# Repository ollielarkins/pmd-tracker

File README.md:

# PMD Tracker

A wearable performance tracker for rugby. It sits in a jersey pouch between the shoulder blades, records a player's match, and syncs the results to a companion app for review after the game.

*KiCad 3D render of the 45 x 30 mm 4-layer board (not yet fabricated).*

## What it measures

| Area | Metrics |
|---|---|
| Locomotion | distance, max speed, sprint count and sprint distance |
| Contact load | impact count, peak g, total load, impacts by intensity band |
| Position | time-on-pitch heatmap (10 m cells), work rate in m/min |

## How it works

1. **Sensing.** A u-blox MAX-M10S GNSS module gives position at 10 Hz. An ADXL372 high-g accelerometer (±200 g) catches impacts that a normal IMU would clip. An LSM6DSO 6-axis IMU is part of the design but is not used by the metrics yet.
2. **On-device metrics.** The nRF52840 runs Zephyr RTOS. Every fix and accel sample goes through [`firmware/lib/metrics`](firmware/lib/metrics), which is portable C:
   - **Position.** Each fix is projected to metres from a pitch origin.
   - **Distance.** Fixes that imply more than 12 m/s are rejected as GNSS glitches. Steps under 0.3 m/s count as standing jitter and add no distance.
   - **Speed and sprints.** Speed is an exponential moving average. A sprint starts above 7 m/s and ends below 6 m/s. It only counts if it lasts at least 1 s.
   - **Impacts.** An impact starts when |a| ≥ 8 g. Samples in the next 250 ms count as the same hit, and its peak is the hit's intensity.
   - **Heatmap.** The time spent at each position is binned into a grid in the pitch frame.
3. **Storage.** A summary checkpoint is written to flash (NVS) every 10 s, so a battery pull mid-match keeps the totals.
4. **Sync.** The device advertises over Bluetooth LE as `PMD`. The app reads one 228-byte summary characteristic (layout in [`metrics.h`](firmware/lib/metrics/metrics.h)). It writes the reset characteristic to start a new session.

Every threshold above sits in one `pmd_config` struct. They are starting values and still need calibrating against real sessions.

## Design targets

The device is designed against World Rugby Law 4.3(m), Regulation 12 and the Player Monitoring Device Performance Specification:

- total mass under 90 g
- no surface radius below 12 mm
- enclosure survives the specification's impact test and 2.5 kN compression test without rupture

| Part | Component |
|---|---|
| MCU | nRF52840 (BLE 5) in a Raytac MDBT50Q-1MV2 module, on a custom 4-layer PCB |
| GNSS | u-blox MAX-M10S, 10 Hz |
| High-g accel | ADXL372 |
| IMU | LSM6DSO |
| Battery | 500 mAh LiPo |

The BOM is in [`hardware/bom.csv`](hardware/bom.csv).

## Hardware

The board is a 45 x 30 mm, 4-layer PCB designed in KiCad 10: [`hardware/kicad`](hardware/kicad).

| Layer | Use |
|---|---|
| F.Cu | parts, signals, GND pour |
| In1.Cu | solid GND plane |
| In2.Cu | 3V3 plane |
| B.Cu | signals, GND pour |

**Power.** USB-C (5.1 kΩ CC pull-downs, so any USB-C charger works) feeds an MCP73831 charger set to about 213 mA (0.4C for the 500 mAh cell). The cell feeds an AP2112K 3.3 V LDO for everything. The GNSS module can draw up to 100 mA at start-up, more than the nRF52840's internal regulator can supply to external parts. A red LED shows charging, and a 1 MΩ / 1 MΩ divider lets firmware read the battery voltage.

**RF.** The module's antenna sits at the top edge, over the footprint's copper keepout. GNSS uses a passive antenna on a u.FL connector next to the MAX-M10S RF pin. The receiver has its own LNA and SAW filter.

**Debug.** SWD on a Tag-Connect TC2030-NL footprint, so there's no connector to fit.

| Signal | nRF52840 pin | To |
|---|---|---|
| SPI SCK / MOSI / MISO | P0.13 / P0.15 / P0.17 | ADXL372, LSM6DSO |
| ADXL372 CS / INT1 | P0.20 / P0.24 | U3 |
| LSM6DSO CS / INT1 | P0.22 / P1.09 | U4 |
| UART TX / RX | P0.06 / P0.08 | MAX-M10S RXD / TXD |
| GNSS reset | P0.27 | MAX-M10S RESET_N |
| Battery sense | P0.04 (AIN2) | VBAT / 2 |
| Status LED | P0.31 | D1 |
| USB D+ / D- | module USB pins | USB-C |

Everything is generated from one file, [`hardware/design.py`](hardware/design.py): parts, nets, placement and track widths. [`hardware/build.sh`](hardware/build.sh) then runs the pipeline:

1. Write the schematic.
2. Run ERC, then check the schematic netlist against `design.py`.
3. Place the parts and add the planes.
4. Autoroute with Freerouting.
5. Run DRC, including schematic parity.
6. Export Gerbers, drill files, the BOM and the renders.

Current results:

- ERC: 0 violations.
- DRC: 0 errors and 0 unconnected items. The only 2 warnings are cosmetic: the USB-C footprint's silkscreen is clipped where the receptacle sits flush with the board edge.
- Schematic parity: 0 issues.

Freerouting gives a different result each run, so `build.sh` retries routing (up to 5 times) until DRC passes, and fails if it never does. The committed board is a checked run.

**Off-board parts** (not on the BOM):

- a 500 mAh single-cell LiPo with a JST PH 2-pin plug
- a passive GNSS patch antenna on a U.FL pigtail
- a Tag-Connect TC2030-NL cable for programming

**Known limits.** There's no power switch: the LDO enable is tied to VBAT, and the firmware doesn't yet use System OFF or GNSS standby, so the cell drains between matches. The board hasn't been fabricated, so nothing here is RF-tested or weighed against the 90 g target.

The ADXL372 footprint isn't in the KiCad library. It's drawn from the land pattern in the ADXL372 datasheet (Rev. C, Figure 111).

Fabrication files: [`hardware/fab/pmd-tracker-gerbers.zip`](hardware/fab/pmd-tracker-gerbers.zip). Design rules are 0.127 mm minimum track and space with 0.6 / 0.3 mm vias, which a standard 4-layer prototype service can make.

## Design images

All of these are exported straight from the KiCad project by [`docs/make_images.sh`](docs/make_images.sh). The board hasn't been fabricated yet, so they're renders and plots, not photos.

| | |
|---|---|
|  Top render |  Bottom render |
|  Isometric, front |  Isometric, back |
|  Side profile |  LSM6DSO + ADXL372 close-up |
|  Charger + LDO close-up |  ADXL372 footprint (from datasheet land pattern) |
|  F.Cu (top copper) |  In1.Cu (GND plane) |
|  In2.Cu (3V3 plane) |  B.Cu (bottom copper) |
|  Assembly drawing |  Block diagram |

Full schematic: [`docs/images/08-schematic.png`](docs/images/08-schematic.png)

## Repository layout

```
firmware/
  lib/metrics/     portable C metrics + host self-test
  src/main.c       Zephyr app: sensors, GNSS, flash checkpoint, BLE service
  boards/          devicetree overlay (nRF52840-DK bring-up wiring)
hardware/
  design.py        parts, nets, placement (single source of truth)
  generate.py      writes the KiCad schematic, libraries and PCB
  build.sh         generate -> ERC -> route -> DRC -> fab outputs
  kicad/           KiCad 10 project (.kicad_sch, .kicad_pcb, custom parts)
  fab/             Gerbers + drill, zipped
  bom.csv
docs/
  block-diagram.svg
  board-top.png, board-bottom.png
  images/          15 design images (renders, schematic, layer plots)
  make_images.sh
```

## Building

Test the metrics on a PC. Any C compiler works:

```
cd firmware/lib/metrics
cc -std=c11 -Wall test_metrics.c metrics.c -lm -o test && ./test
```

Build the firmware (needs Zephyr 4.x and `west`). The nRF52840-DK overlay is used for bring-up:

```
west build -b nrf52840dk/nrf52840 firmware
west flash
```

## Status

- [x] Metrics library with a host self-test
- [ ] Zephyr firmware: GNSS, high-g accel, flash checkpoint, BLE sync (written, not yet built against Zephyr or run on hardware)
- [x] PCB schematic and layout (KiCad): ERC and DRC clean, autorouted. Not yet fabricated or tested.
- [x] Gerbers and drill files
- [ ] Zephyr board definition for the custom PCB. The current overlay targets the nRF52840-DK; see the pin map above.
- [ ] Enclosure
- [ ] Companion app

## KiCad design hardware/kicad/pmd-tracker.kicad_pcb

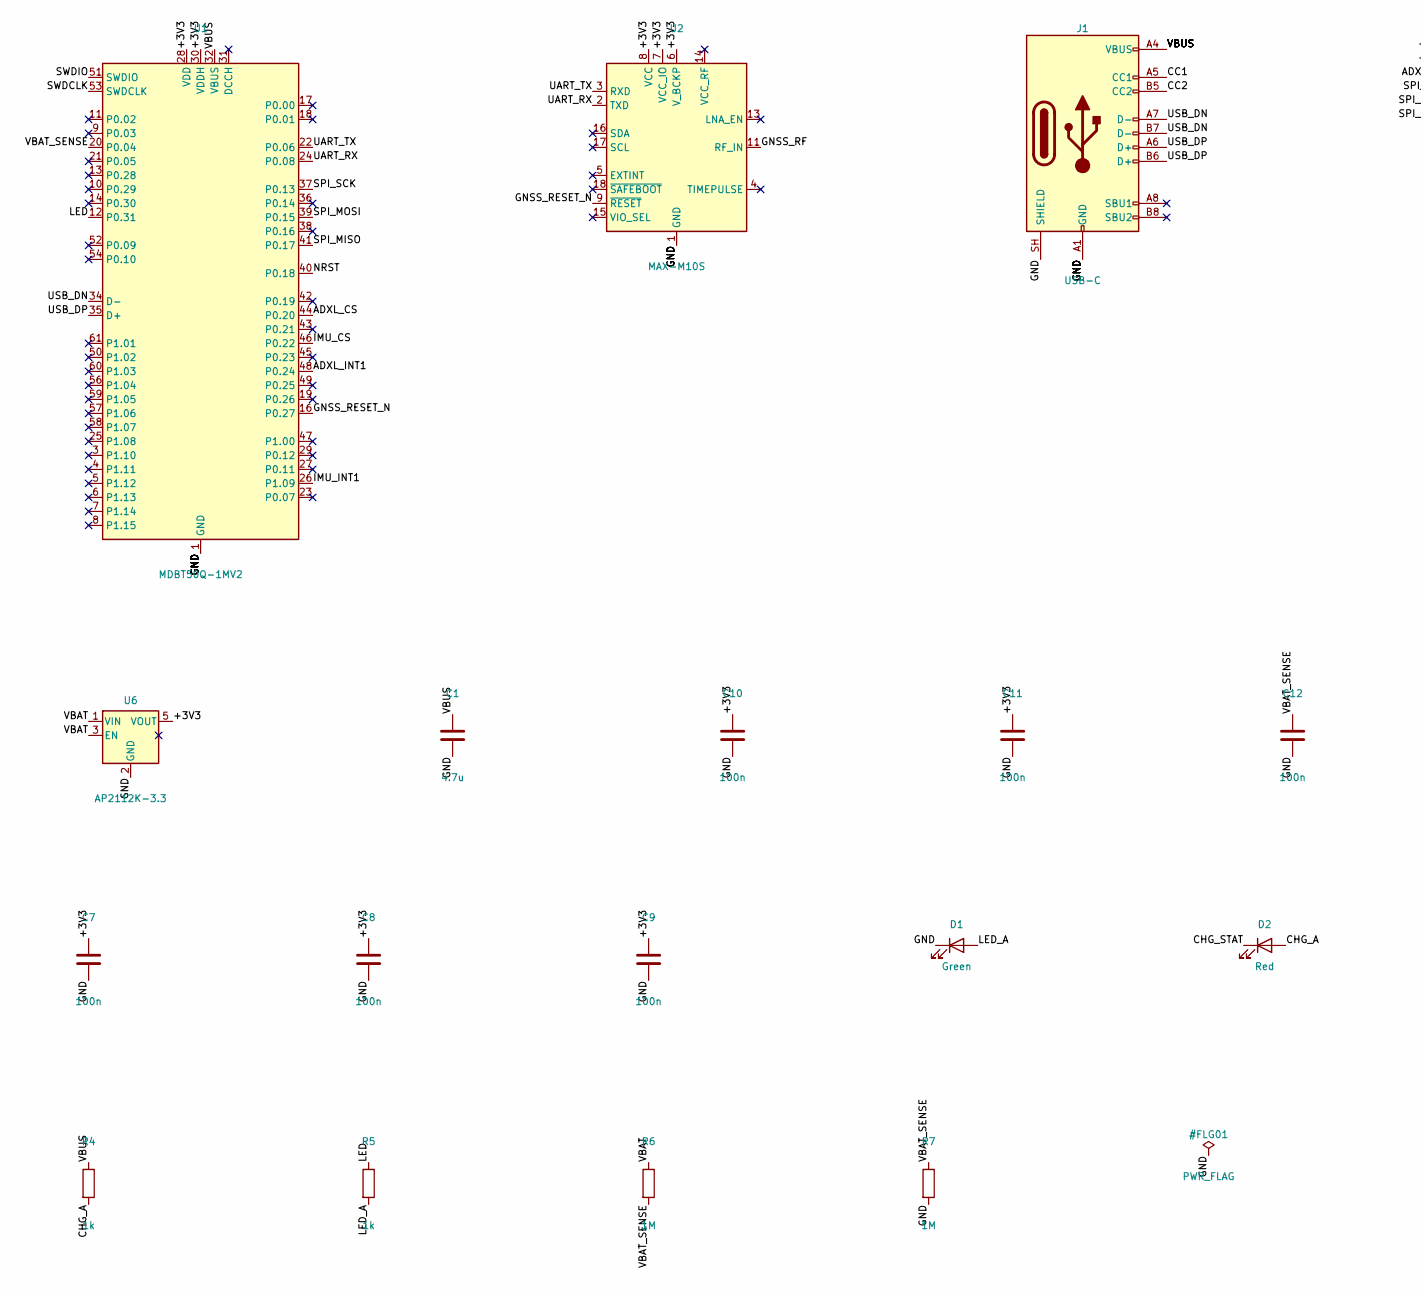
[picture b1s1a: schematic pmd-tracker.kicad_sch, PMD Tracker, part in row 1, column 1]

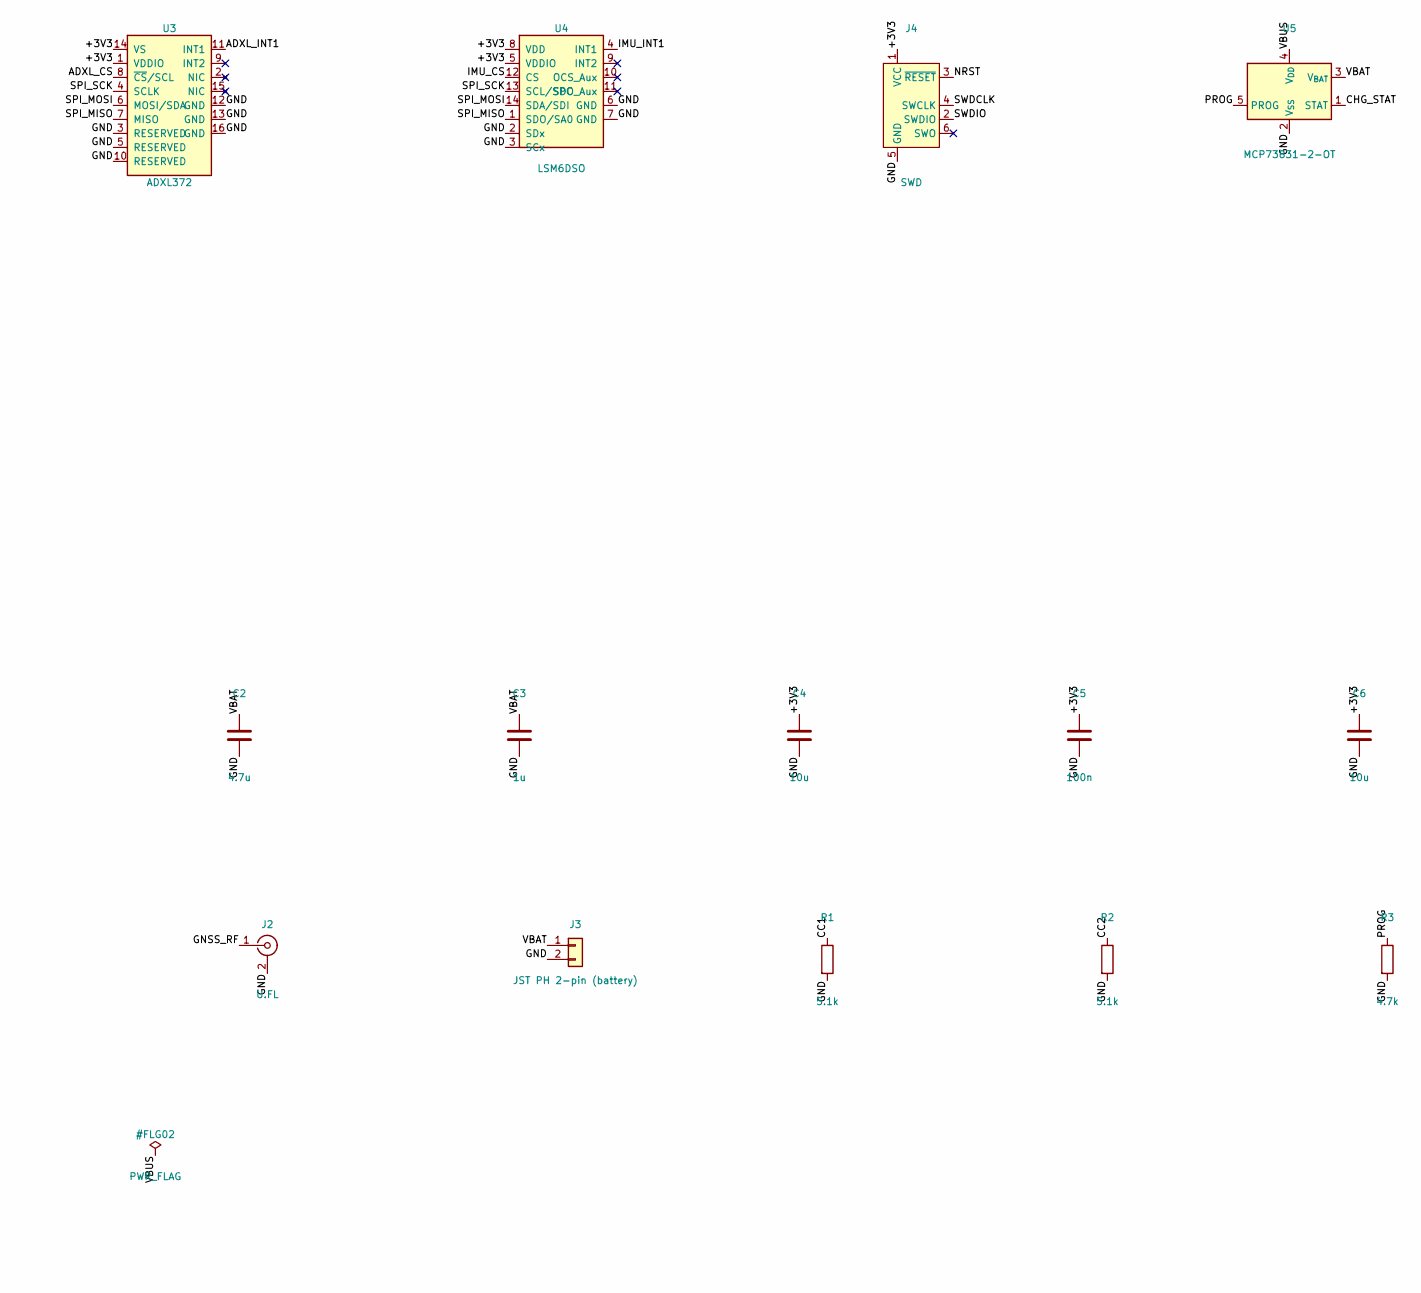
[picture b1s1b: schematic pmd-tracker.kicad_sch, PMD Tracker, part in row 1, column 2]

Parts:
C1, C2: 4.7u; C_0603_1608Metric
C3: 1u; C_0402_1005Metric
C4, C6: 10u; C_0603_1608Metric
C5, C7, C8, C9, C10, C11, C12: 100n; C_0402_1005Metric
D1: Green; LED_0603_1608Metric
D2: Red; LED_0603_1608Metric
J1: USB-C; USB_C_Receptacle_HRO_TYPE-C-31-M-12; MPN TYPE-C-31-M-12
J2: U.FL; U.FL_Hirose_U.FL-R-SMT-1_Vertical; MPN U.FL-R-SMT-1(10)
J3: JST PH 2-pin (battery); JST_PH_S2B-PH-SM4-TB_1x02-1MP_P2.00mm_Horizontal; MPN S2B-PH-SM4-TB(LF)(SN)
J4: SWD; Tag-Connect_TC2030-IDC-NL_2x03_P1.27mm_Vertical
R1, R2: 5.1k; R_0402_1005Metric
R3: 4.7k; R_0402_1005Metric
R4, R5: 1k; R_0402_1005Metric
R6, R7: 1M; R_0402_1005Metric
U1: MDBT50Q-1MV2; Raytac_MDBT50Q; MPN MDBT50Q-1MV2
U2: MAX-M10S; ublox_MAX; MPN MAX-M10S-00B
U3: ADXL372; ADI_LGA-16_3x3.25mm_P0.5mm; MPN ADXL372BCCZ-RL7
U4: LSM6DSO; LGA-14_3x2.5mm_P0.5mm_LayoutBorder3x4y; MPN LSM6DSOTR
U5: MCP73831-2-OT; SOT-23-5; MPN MCP73831T-2ACI/OT
U6: AP2112K-3.3; SOT-23-5; MPN AP2112K-3.3TRG1

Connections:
/+3V3: C4.1, C5.1, C6.1, C7.1, C8.1, C9.1, C10.1, C11.1, J4.1 (VCC), U1.28 (VDD), U1.30 (VDDH), U2.6 (V_BCKP), U2.7 (VCC_IO), U2.8 (VCC), U3.1 (VDDIO), U3.14 (VS), U4.5 (VDDIO), U4.8 (VDD), U6.5 (VOUT)
/ADXL_CS: U1.44 (P0.20), U3.8 (~CS/SCL)
/ADXL_INT1: U1.48 (P0.24), U3.11 (INT1)
/CC1: J1.A5 (CC1), R1.1
/CC2: J1.B5 (CC2), R2.1
/CHG_A: D2.2 (A), R4.2
/CHG_STAT: D2.1 (K), U5.1 (STAT)
/GND: C1.2, C2.2, C3.2, C4.2, C5.2, C6.2, C7.2, C8.2, C9.2, C10.2, C11.2, C12.2, D1.1 (K), J1.A1 (GND), J1.A12 (GND), J1.B1 (GND), J1.B12 (GND), J1.SH (SHIELD), J2.2 (Ext), J3.2, J4.5 (GND), R1.2, R2.2, R3.2, R7.2, U1.1 (GND), U1.2 (GND), U1.15 (GND), U1.33 (GND), U1.55 (GND), U2.1 (GND), U2.10 (GND), U2.12 (GND), U3.3 (RESERVED), U3.5 (RESERVED), U3.10 (RESERVED), U3.12 (GND), U3.13 (GND), U3.16 (GND), U4.2 (SDx), U4.3 (SCx), U4.6 (GND), U4.7 (GND), U5.2 (V_{SS}), U6.2 (GND)
/GNSS_RESET_N: U1.16 (P0.27), U2.9 (~RESET)
/GNSS_RF: J2.1 (In), U2.11 (RF_IN)
/IMU_CS: U1.46 (P0.22), U4.12 (CS)
/IMU_INT1: U1.26 (P1.09), U4.4 (INT1)
/LED: R5.1, U1.12 (P0.31)
/LED_A: D1.2 (A), R5.2
/NRST: J4.3 (~RESET), U1.40 (P0.18)
/PROG: R3.1, U5.5 (PROG)
/SPI_MISO: U1.41 (P0.17), U3.7 (MISO), U4.1 (SDO/SA0)
/SPI_MOSI: U1.39 (P0.15), U3.6 (MOSI/SDA), U4.14 (SDA/SDI)
/SPI_SCK: U1.37 (P0.13), U3.4 (SCLK), U4.13 (SCL/SPC)
/SWDCLK: J4.4 (SWCLK), U1.53 (SWDCLK)
/SWDIO: J4.2 (SWDIO), U1.51 (SWDIO)
/UART_RX: U1.24 (P0.08), U2.2 (TXD)
/UART_TX: U1.22 (P0.06), U2.3 (RXD)
/USB_DN: J1.A7 (D-), J1.B7 (D-), U1.34 (D-)
/USB_DP: J1.A6 (D+), J1.B6 (D+), U1.35 (D+)
/VBAT: C2.1, C3.1, J3.1, R6.1, U5.3 (V_{BAT}), U6.1 (VIN), U6.3 (EN)
/VBAT_SENSE: C12.1, R6.2, R7.1, U1.20 (P0.04)
/VBUS: C1.1, J1.A4 (VBUS), J1.A9 (VBUS), J1.B4 (VBUS), J1.B9 (VBUS), R4.1, U1.32 (VBUS), U5.4 (V_{DD})

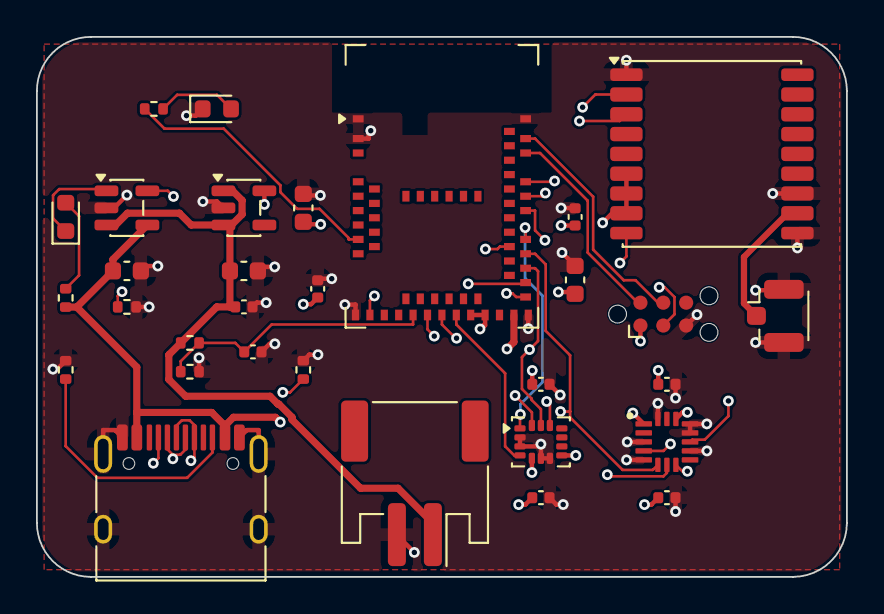
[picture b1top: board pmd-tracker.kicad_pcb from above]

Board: 4 copper layers, 45.0 x 30.0 mm, 31 parts (0 on the bottom side), 28 nets.

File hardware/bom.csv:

"Reference","Value","MPN","Footprint","Qty"
"C1,C2","4.7u","","Capacitor_SMD:C_0603_1608Metric","2"
"C3","1u","","Capacitor_SMD:C_0402_1005Metric","1"
"C4,C6","10u","","Capacitor_SMD:C_0603_1608Metric","2"
"C5,C7-C12","100n","","Capacitor_SMD:C_0402_1005Metric","7"
"D1","Green","","LED_SMD:LED_0603_1608Metric","1"
"D2","Red","","LED_SMD:LED_0603_1608Metric","1"
"J1","USB-C","TYPE-C-31-M-12","Connector_USB:USB_C_Receptacle_HRO_TYPE-C-31-M-12","1"
"J2","U.FL","U.FL-R-SMT-1(10)","Connector_Coaxial:U.FL_Hirose_U.FL-R-SMT-1_Vertical","1"
"J3","JST PH 2-pin (battery)","S2B-PH-SM4-TB(LF)(SN)","Connector_JST:JST_PH_S2B-PH-SM4-TB_1x02-1MP_P2.00mm_Horizontal","1"
"R1,R2","5.1k","","Resistor_SMD:R_0402_1005Metric","2"
"R3","4.7k","","Resistor_SMD:R_0402_1005Metric","1"
"R4,R5","1k","","Resistor_SMD:R_0402_1005Metric","2"
"R6,R7","1M","","Resistor_SMD:R_0402_1005Metric","2"
"U1","MDBT50Q-1MV2","MDBT50Q-1MV2","RF_Module:Raytac_MDBT50Q","1"
"U2","MAX-M10S","MAX-M10S-00B","RF_GPS:ublox_MAX","1"
"U3","ADXL372","ADXL372BCCZ-RL7","pmd:ADI_LGA-16_3x3.25mm_P0.5mm","1"
"U4","LSM6DSO","LSM6DSOTR","Package_LGA:LGA-14_3x2.5mm_P0.5mm_LayoutBorder3x4y","1"
"U5","MCP73831-2-OT","MCP73831T-2ACI/OT","Package_TO_SOT_SMD:SOT-23-5","1"
"U6","AP2112K-3.3","AP2112K-3.3TRG1","Package_TO_SOT_SMD:SOT-23-5","1"
